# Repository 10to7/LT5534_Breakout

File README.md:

LT5534_Breakout
===============

**Warning** _currently untested, may contain errors._

A breakout board for the LT5534 RF power detector.

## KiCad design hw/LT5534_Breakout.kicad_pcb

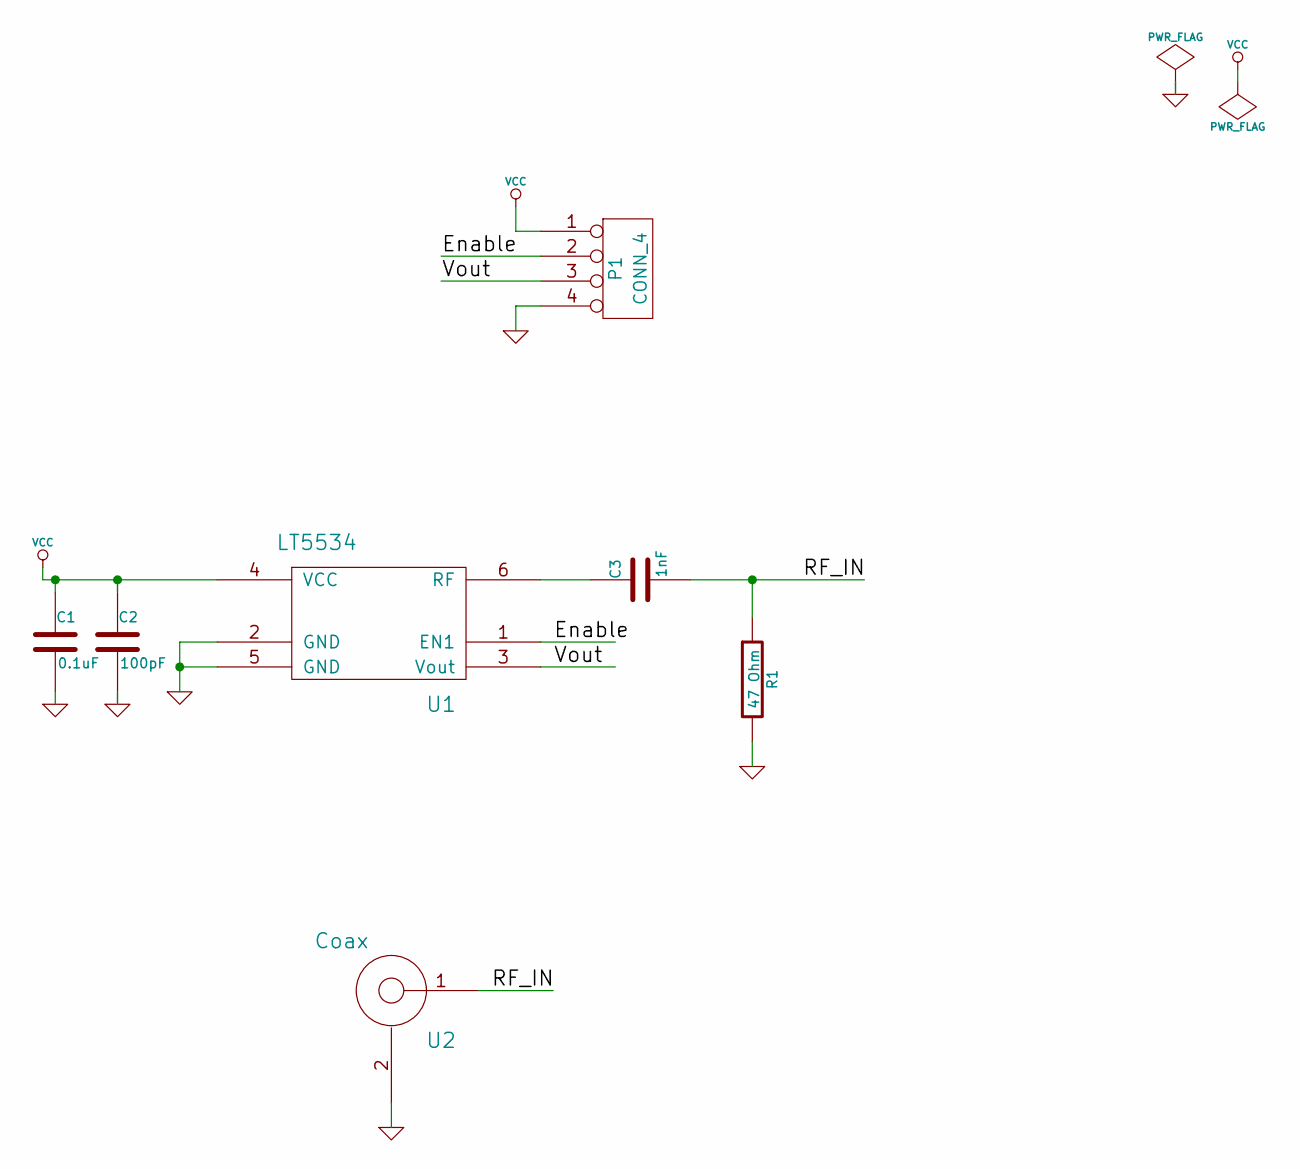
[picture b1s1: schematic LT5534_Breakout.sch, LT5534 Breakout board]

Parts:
C1: 0.1uF
C2: 100pF
C3: 1nF
P1: CONN_4
R1: 47 Ohm
U1: LT5534
U2: Coax

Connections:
/Enable: P1.2, U1.1 (EN1)
/RF_IN: C3.2, R1.1, U2.1
/Vout: P1.3, U1.3 (Vout)
GND: C1.2, C2.2, P1.4, R1.2, U1.2 (GND), U1.5 (GND), U2.2
unnamed: C3.1, U1.6 (RF)
VCC: C1.1, C2.1, P1.1, U1.4 (VCC)

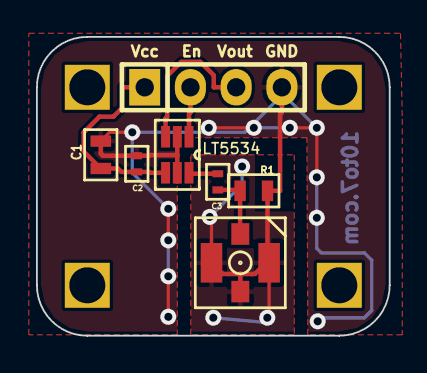
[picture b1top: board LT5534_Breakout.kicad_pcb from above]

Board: 2 copper layers, 19.6 x 16.6 mm, 11 parts (0 on the bottom side), 6 nets.

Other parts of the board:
2mmHole_1, 2mmHole_2, 2mmHole_3, 2mmHole_4: VAL**; 2mmHole

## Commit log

2014-05-26 Schematic created, patial netlist implmented. Needs a SC70 and U.FL footprints to be created.
2014-05-27 Board completed, version 0.1 sent to fab house
